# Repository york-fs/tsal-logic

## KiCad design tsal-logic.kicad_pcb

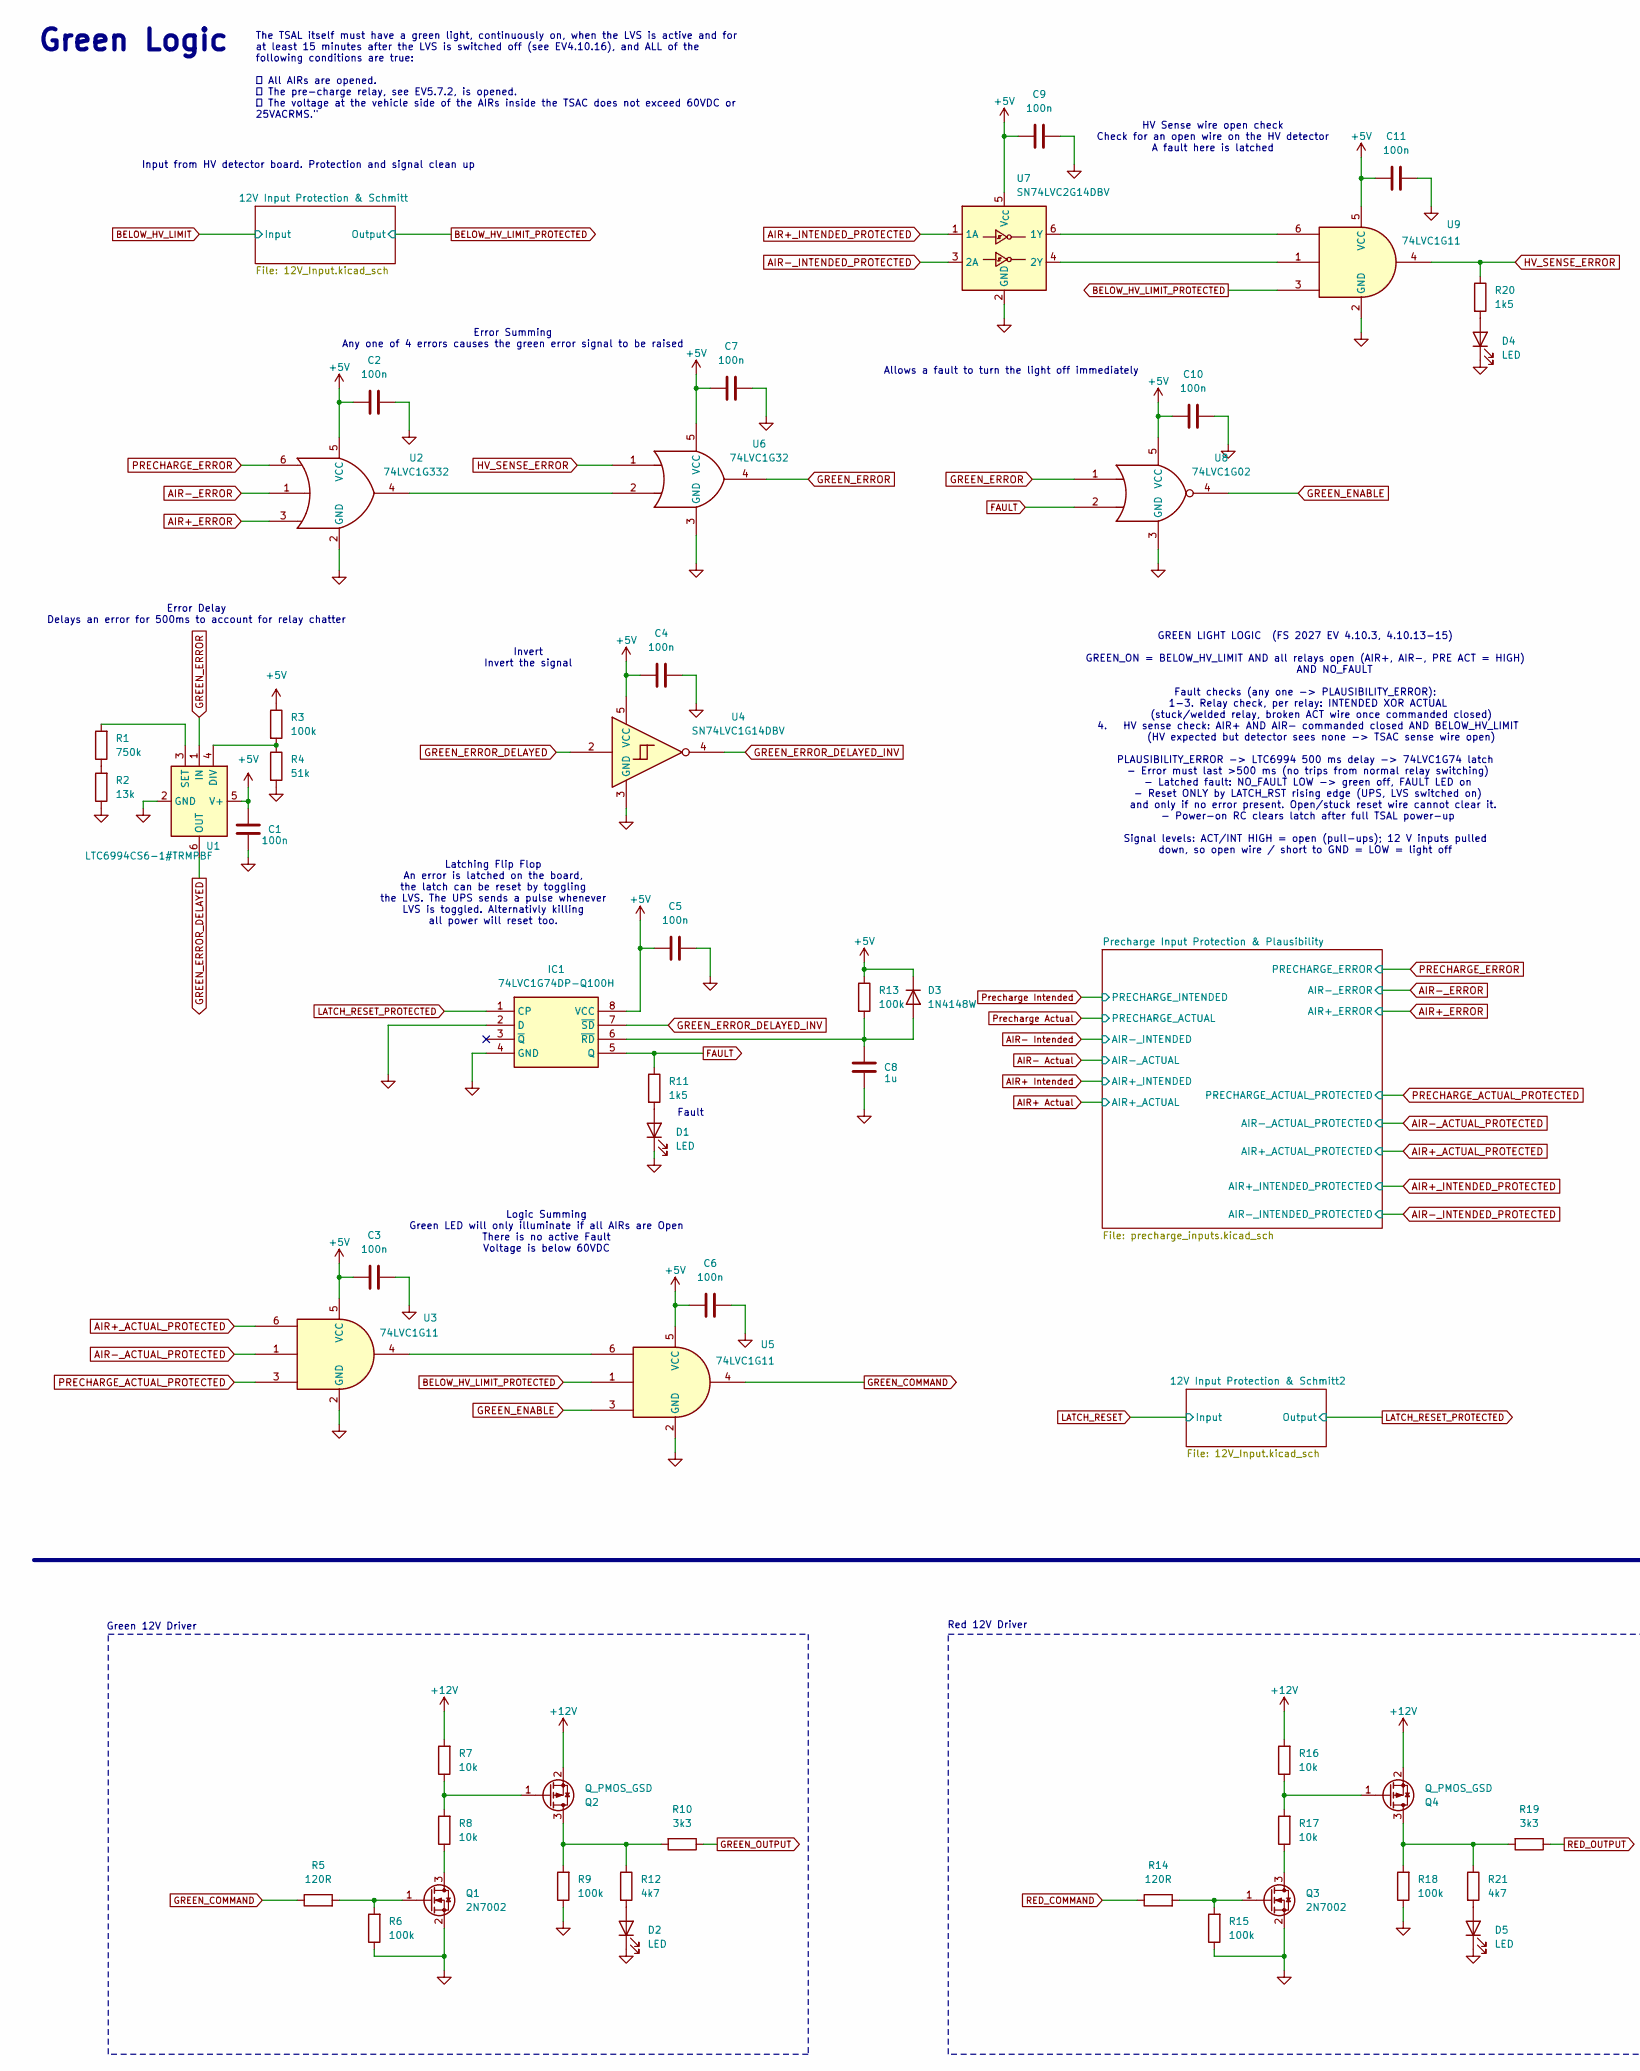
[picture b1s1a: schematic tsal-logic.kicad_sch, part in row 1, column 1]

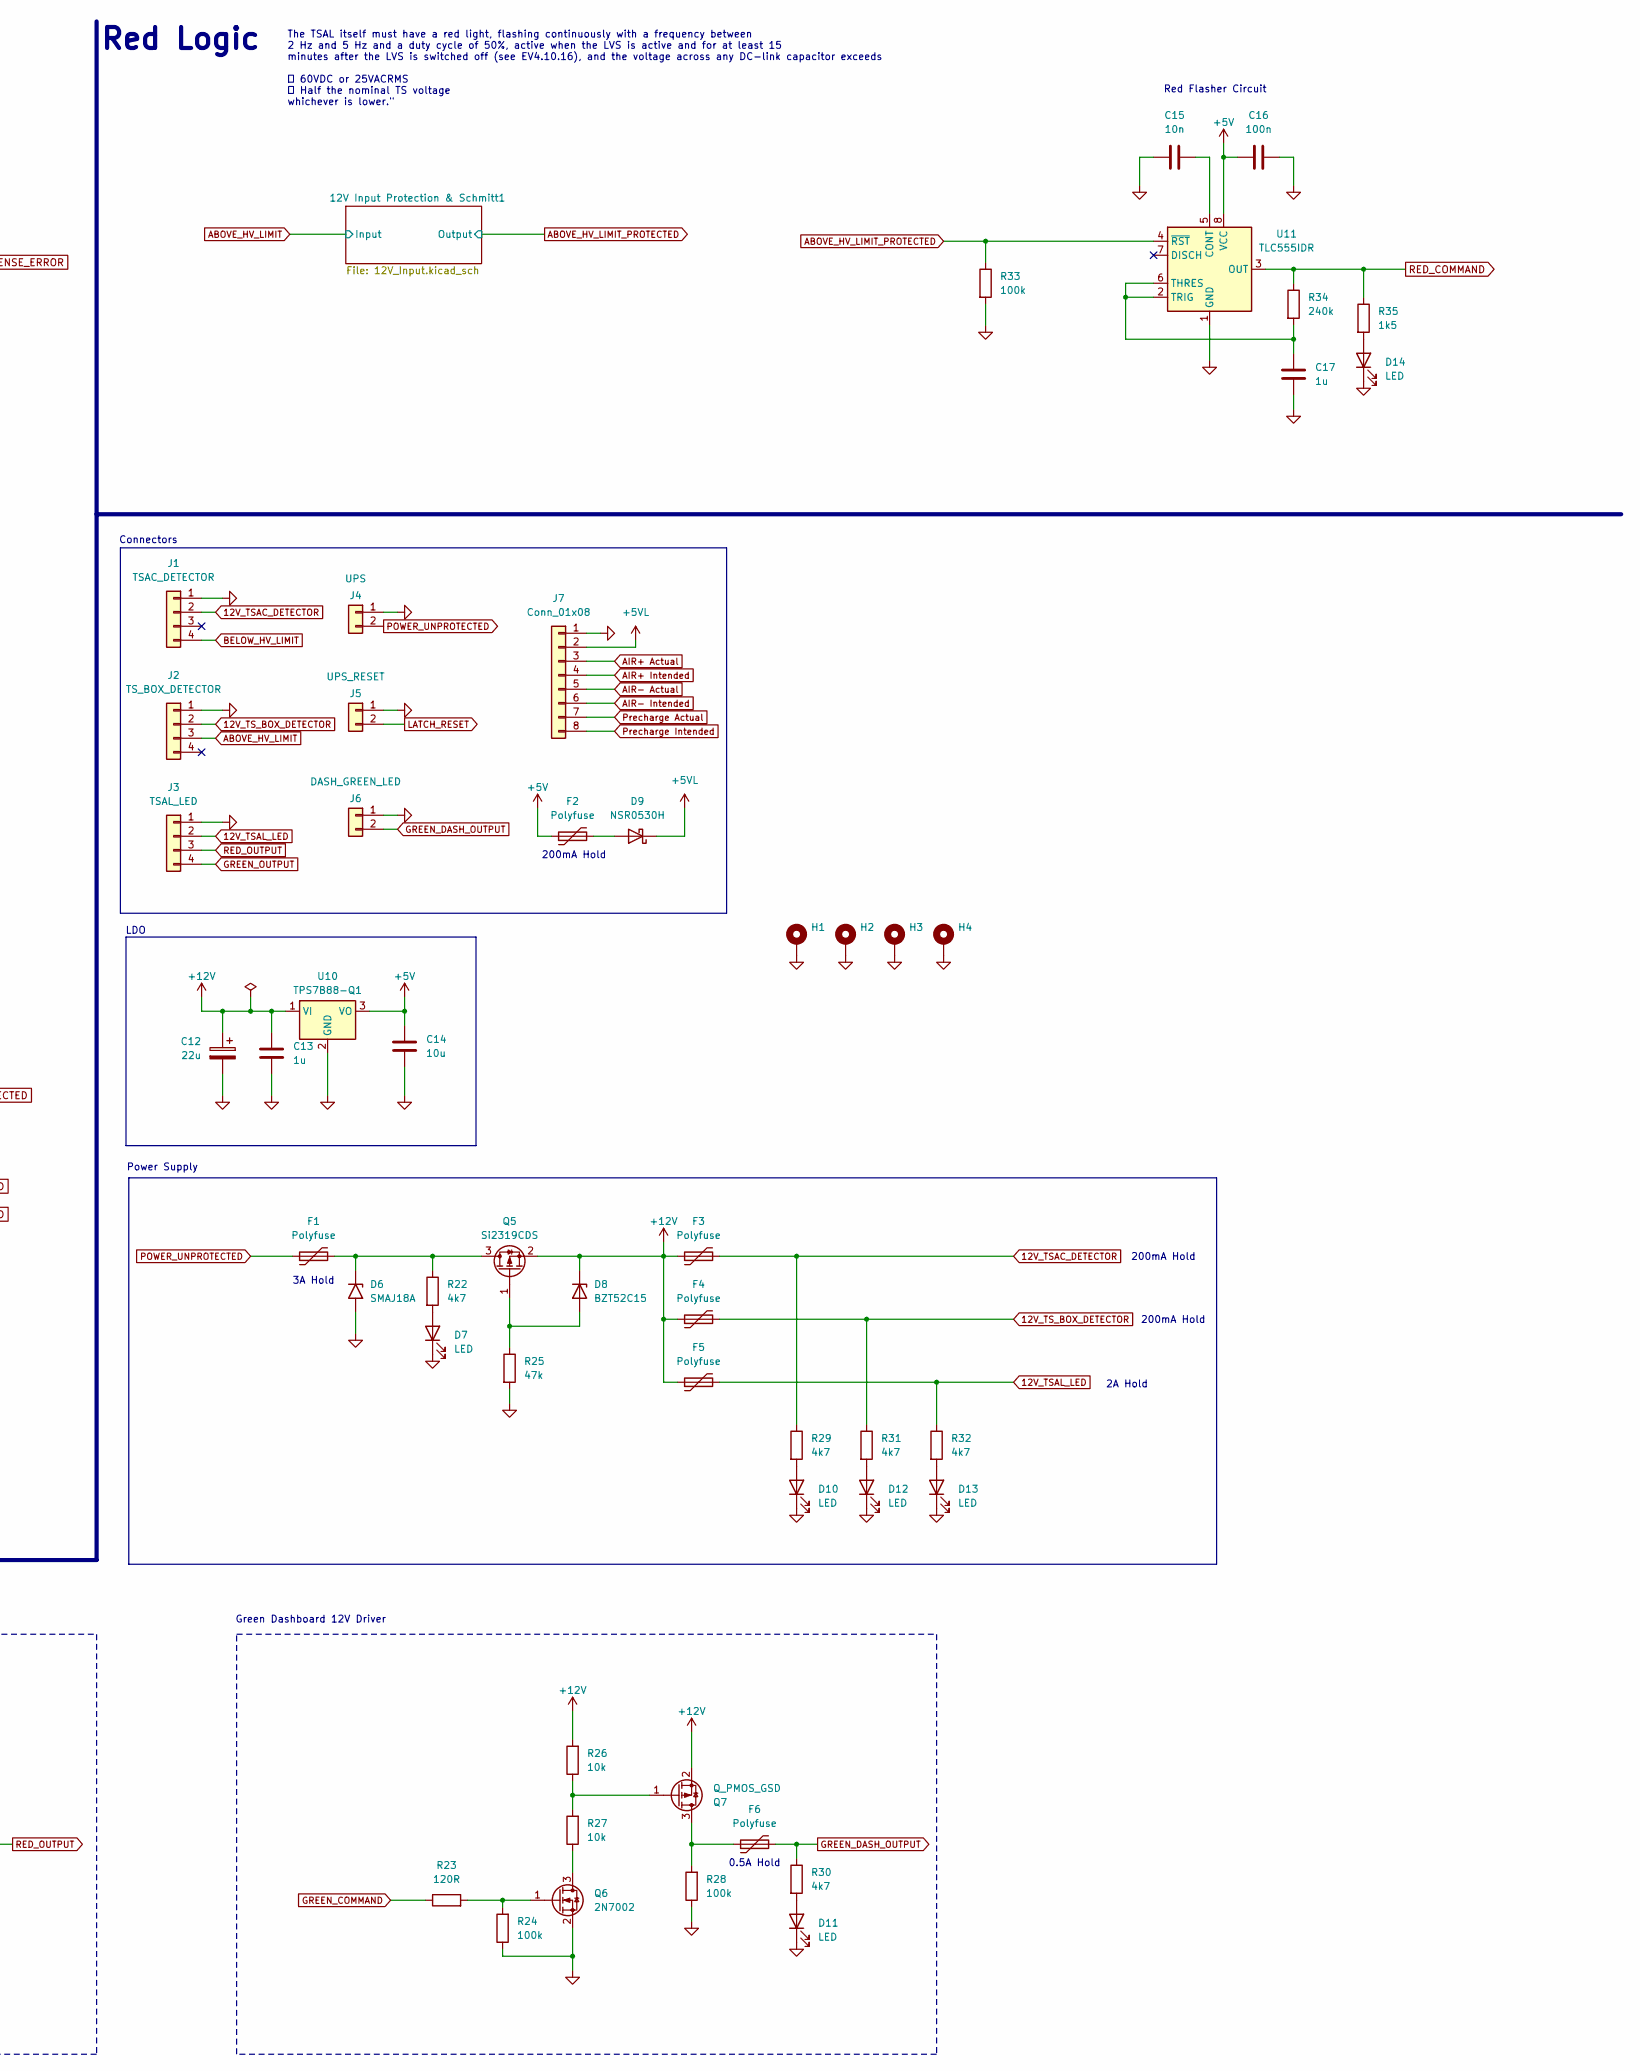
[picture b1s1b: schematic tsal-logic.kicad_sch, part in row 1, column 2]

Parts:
C1, C2, C3, C4, C5, C6, C7, C9, C10, C11, C16: 100n; C_0603_1608Metric
C8, C17: 1u; C_1206_3216Metric
C12: 22u; CP_Elec_6.3x5.8
C13: 1u; C_0603_1608Metric
C14: 10u; C_1206_3216Metric
C15: 10n; C_0603_1608Metric
D1, D2, D4, D5, D7, D10, D11, D12, D13, D14: LED; LED_0603_1608Metric
D3: 1N4148W; D_SOD-123
D6: SMAJ18A; D_SMA
D8: BZT52C15; D_SOD-123; LCSC C19077412
D9: NSR0530H; D_SOD-323F
F1: Polyfuse; Fuse_2920_7451Metric
F2, F3, F4, F6: Polyfuse; Fuse_0805_2012Metric
F5: Polyfuse; Fuse_1210_3225Metric
H1, H2, H3, H4: MountingHole_Pad; MountingHole_3.2mm_M3_Pad_Via
IC1: 74LVC1G74DP-Q100H; TSSOP-8_3x3mm_P0.65mm; Mouser Part Number 771-74LVC1G74DPQ100H
J1: TSAC_DETECTOR; MolexMicrofitPlus1x4
J2: TS_BOX_DETECTOR; MolexMicrofitPlus1x4
J3: TSAL_LED; MolexMicrofitPlus1x4
J4: UPS; MolexMicrofitPlus1x2
J5: UPS_RESET; MolexMicrofitPlus1x2
J6: DASH_GREEN_LED; MolexMicrofitPlus1x2
J7: Conn_01x08; MolexMicrofitPlus2x4
Q1, Q3, Q6: 2N7002; SOT-23
Q2, Q4, Q7: Q_PMOS_GSD; SOT-23; LCSC C150147
Q5: Si2319CDS; SOT-23; LCSC C150147
R1: 750k; R_0603_1608Metric
R2: 13k; R_0603_1608Metric
R3, R6, R9, R13, R15, R18, R24, R28, R33: 100k; R_0603_1608Metric
R4: 51k; R_0603_1608Metric
R5, R14, R23: 120R; R_0603_1608Metric
R7, R8, R16, R17, R26, R27: 10k; R_0603_1608Metric
R10, R19: 3k3; R_0603_1608Metric
R11, R20, R35: 1k5; R_0603_1608Metric
R12, R21, R22, R29, R30, R31, R32: 4k7; R_0603_1608Metric
R25: 47k; R_0603_1608Metric
R34: 240k; R_0603_1608Metric
U1: LTC6994CS6-1#TRMPBF; TSOT-23-6
U2: 74LVC1G332; SOT-23-6
U3, U5, U9: 74LVC1G11; SOT-23-6
U4: SN74LVC1G14DBV; SOT-23-5
U6: 74LVC1G32; SOT-23-5
U7: SN74LVC2G14DBV; SOT-23-6
U8: 74LVC1G02; SOT-23-5
U10: TPS7B88-Q1; TO-252-2
U11: TLC555IDR; SOIC-8_3.9x4.9mm_P1.27mm

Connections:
12V_TSAC_DETECTOR: F3.2, J1.2, R29.1
12V_TSAL_LED: F5.2, J3.2, R32.1
12V_TS_BOX_DETECTOR: F4.2, J2.2, R31.1
+5V: C1.2, C2.1, C3.1, C4.1, C5.1, C6.1, C7.1, C9.1, C10.1, C11.1, C14.1, C16.1, D3.1 (K), F2.1, IC1.8 (VCC), R3.1, R13.1, U1.5 (V+), U2.5 (VCC), U3.5 (VCC), U4.5 (VCC), U5.5 (VCC), U6.5 (VCC), U7.5 (V_{CC}), U8.5 (VCC), U9.5 (VCC), U10.3 (VO), U11.8 (VCC); also elsewhere on the board
+5VL: D9.1 (K), J7.2
+12V: C12.1, C13.1, D8.1 (K), F3.1, F4.1, F5.1, Q2.2 (S), Q4.2 (S), Q5.2 (S), Q7.2 (S), R7.2, R16.2, R26.2, U10.1 (VI)
ABOVE_HV_LIMIT: J2.3; also elsewhere on the board
ABOVE_HV_LIMIT_PROTECTED: R33.1, U11.4 (~RST); also elsewhere on the board
AIR+ Actual: J7.3; also elsewhere on the board
AIR+ Intended: J7.4; also elsewhere on the board
AIR+_ACTUAL_PROTECTED: U3.6; also elsewhere on the board
AIR+_ERROR: U2.3; also elsewhere on the board
AIR+_INTENDED_PROTECTED: U7.1 (1A); also elsewhere on the board
AIR- Actual: J7.5; also elsewhere on the board
AIR- Intended: J7.6; also elsewhere on the board
AIR-_ACTUAL_PROTECTED: U3.1; also elsewhere on the board
AIR-_ERROR: U2.1; also elsewhere on the board
AIR-_INTENDED_PROTECTED: U7.3 (2A); also elsewhere on the board
BELOW_HV_LIMIT: J1.4; also elsewhere on the board
BELOW_HV_LIMIT_PROTECTED: U5.1, U9.3; also elsewhere on the board
FAULT: IC1.5 (Q), R11.1, U8.2
GND: C1.1, C2.2, C3.2, C4.2, C5.2, C6.2, C7.2, C8.1, C9.2, C10.2, C11.2, C12.2, C13.2, C14.2, C15.1, C16.2, C17.1, D1.1 (K), D2.1 (K), D4.1 (K), D5.1 (K), D6.2 (A2), D7.1 (K), D10.1 (K), D11.1 (K), D12.1 (K), D13.1 (K), D14.1 (K), H1.1 (1_1), H2.1 (1_1), H3.1 (1_1), H4.1 (1_1), IC1.2 (D), IC1.4 (GND), J1.1, J2.1, J3.1, J4.1, J5.1, J6.1, J7.1, Q1.2 (S), Q3.2 (S), Q6.2 (S), R2.1, R4.2, R6.1, R9.1, R15.1, R18.1, R24.1, R25.2, R28.1, R33.2, U1.2 (GND), U2.2 (GND), U3.2 (GND), U4.3 (GND), U5.2 (GND), U6.3 (GND), U7.2 (GND), U8.3 (GND), U9.2 (GND), U10.2 (GND), U11.1 (GND); also elsewhere on the board
GREEN_COMMAND: R5.1, R23.1, U5.4
GREEN_DASH_OUTPUT: F6.2, J6.2, R30.1
GREEN_ENABLE: U5.3, U8.4
GREEN_ERROR: U1.1 (IN), U6.4, U8.1
GREEN_ERROR_DELAYED: U1.6 (OUT), U4.2
GREEN_ERROR_DELAYED_INV: IC1.7 (~SD), U4.4
GREEN_OUTPUT: J3.4, R10.1
HV_SENSE_ERROR: R20.1, U6.1, U9.4
LATCH_RESET: J5.2; also elsewhere on the board
LATCH_RESET_PROTECTED: IC1.1 (CP); also elsewhere on the board
unnamed: D1.2 (A), R11.2
unnamed: D2.2 (A), R12.2
unnamed: C8.2, D3.2 (A), IC1.6 (~RD), R13.2
unnamed: D4.2 (A), R20.2
unnamed: D5.2 (A), R21.2
unnamed: D6.1 (A1), F1.2, Q5.3 (D), R22.1
unnamed: D7.2 (A), R22.2
unnamed: D8.2 (A), Q5.1 (G), R25.1
unnamed: D9.2 (A), F2.2
unnamed: D10.2 (A), R29.2
unnamed: D11.2 (A), R30.2
unnamed: D12.2 (A), R31.2
unnamed: D13.2 (A), R32.2
unnamed: D14.2 (A), R35.2
unnamed: Q1.3 (D), R8.1
unnamed: Q1.1 (G), R5.2, R6.2
unnamed: Q2.3 (D), R9.2, R10.2, R12.1
unnamed: Q2.1 (G), R7.1, R8.2
unnamed: Q3.3 (D), R17.1
unnamed: Q3.1 (G), R14.2, R15.2
unnamed: Q4.3 (D), R18.2, R19.2, R21.1
unnamed: Q4.1 (G), R16.1, R17.2
unnamed: Q6.3 (D), R27.1
unnamed: Q6.1 (G), R23.2, R24.2
unnamed: F6.1, Q7.3 (D), R28.2
unnamed: Q7.1 (G), R26.1, R27.2
unnamed: R1.1, R2.2
unnamed: R3.2, R4.1, U1.4 (DIV)
unnamed: R1.2, U1.3 (SET)
unnamed: U2.4, U6.2
unnamed: U3.4, U5.6
unnamed: U7.6 (1Y), U9.6
unnamed: U7.4 (2Y), U9.1
unnamed: C15.2, U11.5 (CONT)
unnamed: C17.2, R34.2, U11.2 (TRIG), U11.6 (THRES)
POWER_UNPROTECTED: F1.1, J4.2
PRECHARGE_ACTUAL_PROTECTED: U3.3; also elsewhere on the board
PRECHARGE_ERROR: U2.6; also elsewhere on the board
Precharge Actual: J7.7; also elsewhere on the board
Precharge Intended: J7.8; also elsewhere on the board
RED_COMMAND: R14.1, R34.1, R35.1, U11.3 (OUT)
RED_OUTPUT: J3.3, R19.1

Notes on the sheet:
Latching Flip Flop An error is latched on the board, the latch can be reset by toggling the LVS. The UPS sends a pulse whenever LVS is toggled. Alternativly killing all power will reset too.
0.5A Hold
GREEN LIGHT LOGIC (FS 2027 EV 4.10.3, 4.10.13-15) GREEN_ON = BELOW_HV_LIMIT AND all relays open (AIR+, AIR-, PRE ACT = HIGH) AND NO_FAULT Fault checks (any one -> PLAUSIBILITY_ERROR): 1-3. Relay check, per relay: INTENDED XOR ACTUAL (stuck/welded relay, broken ACT wire once commanded closed) 4. HV 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
200mA Hold
LDO
Error Summing Any one of 4 errors causes the green error signal to be raised
Input from HV detector board. Protection and signal clean up
Power Supply
2A Hold
The TSAL itself must have a green light, continuously on, when the LVS is active and for at least 15 minutes after the LVS is switched off (see EV4.10.16), and ALL of the following conditions are true:  All AIRs are opened.  The pre-charge relay, see EV5.7.2, is opened.  The voltage at the vehic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
HV Sense wire open check Check for an open wire on the HV detector A fault here is latched
Red 12V Driver
Error Delay Delays an error for 500ms to account for relay chatter
Green 12V Driver
Red Flasher Circuit
Invert Invert the signal
Allows a fault to turn the light off immediately
3A Hold
Logic Summing Green LED will only illuminate if all AIRs are Open There is no active Fault Voltage is below 60VDC
Fault
Green Dashboard 12V Driver
The TSAL itself must have a red light, flashing continuously with a frequency between 2 Hz and 5 Hz and a duty cycle of 50%, active when the LVS is active and for at least 15 minutes after the LVS is switched off (see EV4.10.16), and the voltage across any DC-link capacitor exceeds  60VDC or 25VAC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
Connectors
Red Logic
Green Logic

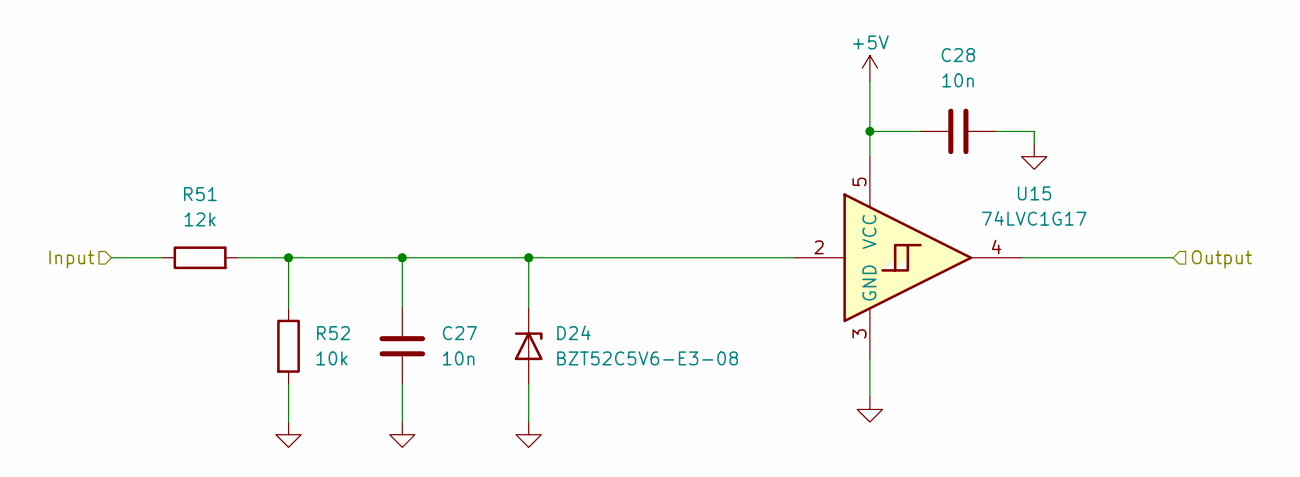
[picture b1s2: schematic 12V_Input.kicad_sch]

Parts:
C27, C28: 10n; C_0603_1608Metric
D24: BZT52C5V6-E3-08; D_SOD-123; LCSC C19077412
R51: 12k; R_0603_1608Metric
R52: 10k; R_0603_1608Metric
U15: 74LVC1G17; SOT-23-5

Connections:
+5V: C28.1, U15.5 (VCC); also elsewhere on the board
BELOW_HV_LIMIT: R51.1; also elsewhere on the board
BELOW_HV_LIMIT_PROTECTED: U15.4; also elsewhere on the board
GND: C27.2, C28.2, D24.2 (A), R52.2, U15.3 (GND); also elsewhere on the board
unnamed: C27.1, D24.1 (K), R51.2, R52.1, U15.2

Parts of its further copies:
C29, C30, C31, C32: 10n; C_0603_1608Metric
D25, D26: BZT52C5V6-E3-08; D_SOD-123; LCSC C19077412
R53, R55: 12k; R_0603_1608Metric
R54, R56: 10k; R_0603_1608Metric
U16, U17: 74LVC1G17; SOT-23-5

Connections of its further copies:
+5V: C30.1, C32.1, U16.5 (VCC), U17.5 (VCC); also elsewhere on the board
ABOVE_HV_LIMIT: R53.1; also elsewhere on the board
ABOVE_HV_LIMIT_PROTECTED: U16.4; also elsewhere on the board
GND: C29.2, C30.2, C31.2, C32.2, D25.2 (A), D26.2 (A), R54.2, R56.2, U16.3 (GND), U17.3 (GND); also elsewhere on the board
LATCH_RESET: R55.1; also elsewhere on the board
LATCH_RESET_PROTECTED: U17.4; also elsewhere on the board
unnamed: C29.1, D25.1 (K), R53.2, R54.1, U16.2
unnamed: C31.1, D26.1 (K), R55.2, R56.1, U17.2

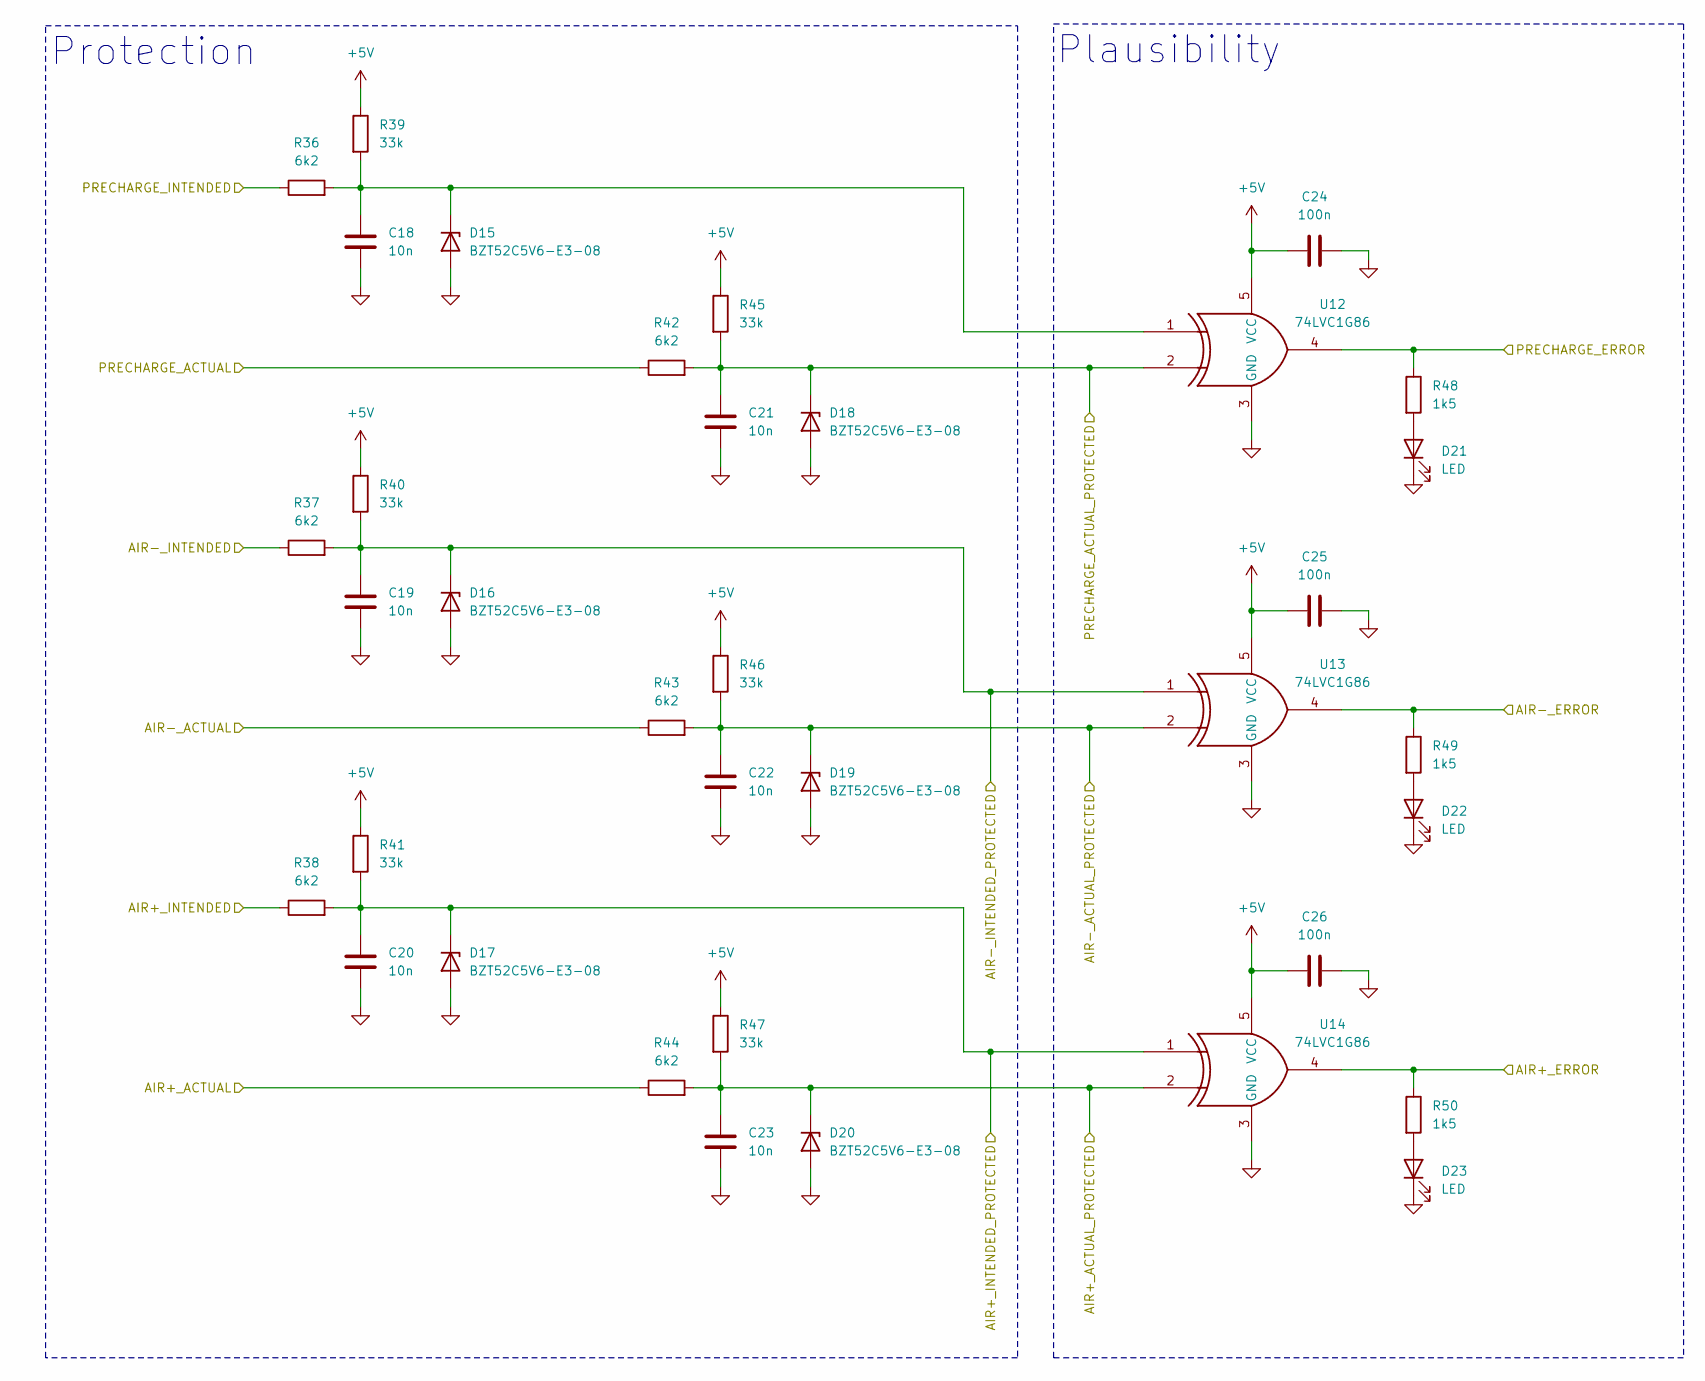
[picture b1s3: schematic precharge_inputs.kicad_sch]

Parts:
C18, C19, C20, C21, C22, C23: 10n; C_0603_1608Metric
C24, C25, C26: 100n; C_0603_1608Metric
D15, D16, D17, D18, D19, D20: BZT52C5V6-E3-08; D_SOD-123; LCSC C19077412
D21, D22, D23: LED; LED_0603_1608Metric
R36, R37, R38, R42, R43, R44: 6k2; R_0603_1608Metric
R39, R40, R41, R45, R46, R47: 33k; R_0603_1608Metric
R48, R49, R50: 1k5; R_0603_1608Metric
U12, U13, U14: 74LVC1G86; SOT-23-5

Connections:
+5V: C24.1, C25.1, C26.1, R39.1, R40.1, R41.1, R45.1, R46.1, R47.1, U12.5 (VCC), U13.5 (VCC), U14.5 (VCC); also elsewhere on the board
AIR+ Actual: R44.1; also elsewhere on the board
AIR+ Intended: R38.1; also elsewhere on the board
AIR+_ACTUAL_PROTECTED: C23.1, D20.1 (K), R44.2, R47.2, U14.2; also elsewhere on the board
AIR+_ERROR: R50.1, U14.4; also elsewhere on the board
AIR+_INTENDED_PROTECTED: C20.1, D17.1 (K), R38.2, R41.2, U14.1; also elsewhere on the board
AIR- Actual: R43.1; also elsewhere on the board
AIR- Intended: R37.1; also elsewhere on the board
AIR-_ACTUAL_PROTECTED: C22.1, D19.1 (K), R43.2, R46.2, U13.2; also elsewhere on the board
AIR-_ERROR: R49.1, U13.4; also elsewhere on the board
AIR-_INTENDED_PROTECTED: C19.1, D16.1 (K), R37.2, R40.2, U13.1; also elsewhere on the board
GND: C18.2, C19.2, C20.2, C21.2, C22.2, C23.2, C24.2, C25.2, C26.2, D15.2 (A), D16.2 (A), D17.2 (A), D18.2 (A), D19.2 (A), D20.2 (A), D21.1 (K), D22.1 (K), D23.1 (K), U12.3 (GND), U13.3 (GND), U14.3 (GND); also elsewhere on the board
unnamed: C18.1, D15.1 (K), R36.2, R39.2, U12.1
unnamed: D21.2 (A), R48.2
unnamed: D22.2 (A), R49.2
unnamed: D23.2 (A), R50.2
PRECHARGE_ACTUAL_PROTECTED: C21.1, D18.1 (K), R42.2, R45.2, U12.2; also elsewhere on the board
PRECHARGE_ERROR: R48.1, U12.4; also elsewhere on the board
Precharge Actual: R42.1; also elsewhere on the board
Precharge Intended: R36.1; also elsewhere on the board

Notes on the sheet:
Plausibility
Protection

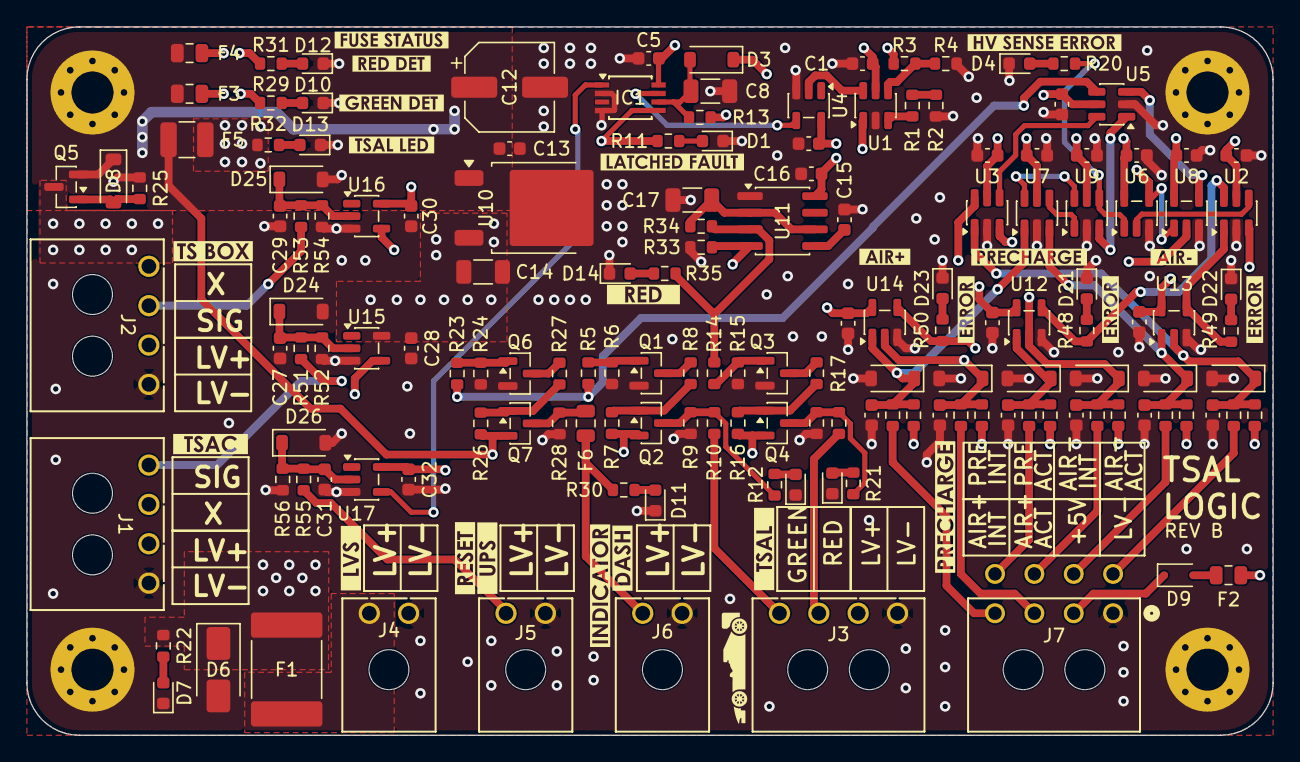
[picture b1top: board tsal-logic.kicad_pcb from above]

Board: 4 copper layers, 95.0 x 54.0 mm, 178 parts (0 on the bottom side), 81 nets.

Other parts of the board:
kibuzzard-6AF2F854: G***; kibuzzard-6AF2F854
kibuzzard-6AF25BAC: G***; kibuzzard-6AF25BAC
kibuzzard-6AF258D0, kibuzzard-6AF258D0#2, kibuzzard-6AF258D0#3: G***; kibuzzard-6AF258D0
kibuzzard-6AF258EB: G***; kibuzzard-6AF258EB
kibuzzard-6AF258FB: G***; kibuzzard-6AF258FB
kibuzzard-6AF345D6: G***; kibuzzard-6AF345D6
kibuzzard-6AF345EE: G***; kibuzzard-6AF345EE
kibuzzard-6AF3020A: G***; kibuzzard-6AF3020A
kibuzzard-6AF3445E: G***; kibuzzard-6AF3445E
kibuzzard-6AF3447E: G***; kibuzzard-6AF3447E
kibuzzard-6AF3449C: G***; kibuzzard-6AF3449C
kibuzzard-6AF3917F: G***; kibuzzard-6AF3917F
kibuzzard-6AF25902: G***; kibuzzard-6AF25902
kibuzzard-6AF25947: G***; kibuzzard-6AF25947
kibuzzard-6AF30218: G***; kibuzzard-6AF30218
kibuzzard-6AF30225: G***; kibuzzard-6AF30225
kibuzzard-6AF34707: G***; kibuzzard-6AF34707
kibuzzard-6AF35645: G***; kibuzzard-6AF35645
kibuzzard-6AF39142: G***; kibuzzard-6AF39142
kibuzzard-6AFB0BD4: G***; kibuzzard-6AFB0BD4

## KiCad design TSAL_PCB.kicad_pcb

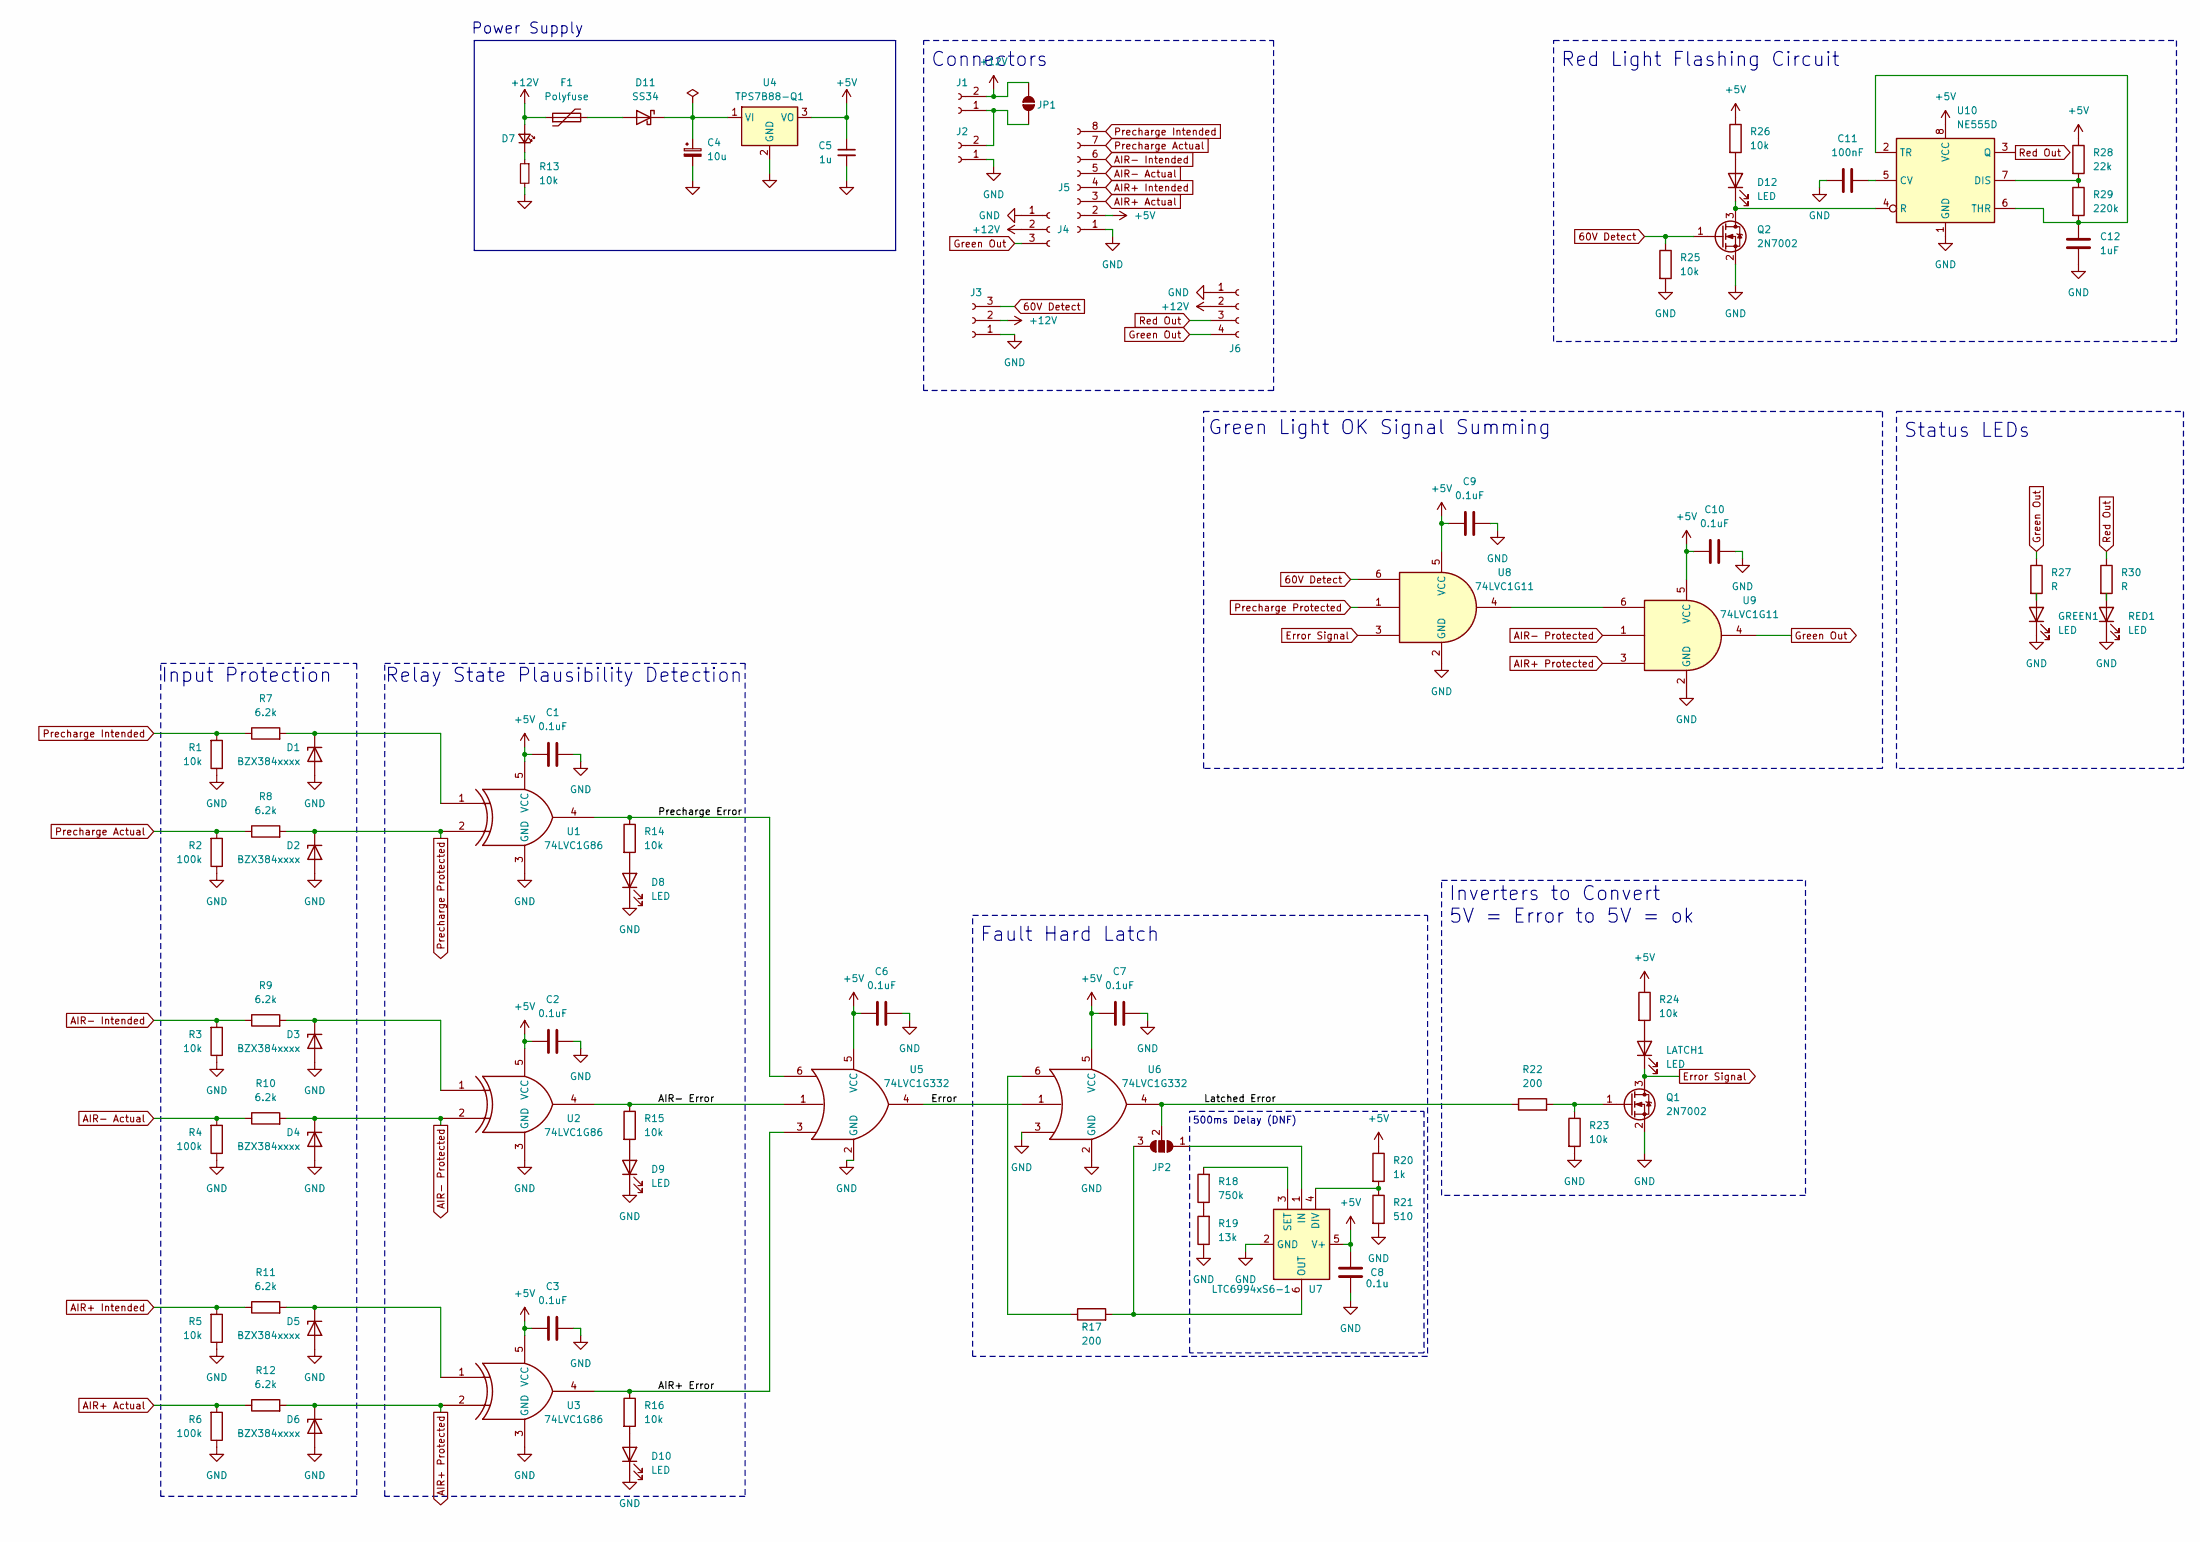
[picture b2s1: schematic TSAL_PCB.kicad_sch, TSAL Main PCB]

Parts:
C1, C2, C3, C6, C7, C9, C10: 0.1uF; C_0603_1608Metric
C4: 10u; CP_Elec_6.3x5.4
C5: 1u; C_0603_1608Metric
C8: 0.1u; C_0603_1608Metric
C11: 100nF; C_0603_1608Metric
C12: 1uF; C_0603_1608Metric
D1, D2, D3, D4, D5, D6: BZX384xxxx; D_SOD-323
D7: LED_Small; LED_0603_1608Metric
D8, D9, D10, D12: LED; LED_0603_1608Metric
D11: SS34; D_SMA
F1: Polyfuse; R_0805_2012Metric
GREEN1: LED; LED_0603_1608Metric
J1, J2: Conn_01x02_Socket; MolexMicrofitPlus1x2
J3, J4: Conn_01x03_Socket; MolexMicrofitPlus1x3
J5: Conn_01x08_Socket; MolexMicrofitPlus1x8
J6: Conn_01x04_Socket; MolexMicrofitPlus1x4
JP1: SolderJumper_2_Open; SolderJumper-2_P1.3mm_Open_RoundedPad1.0x1.5mm
JP2: SolderJumper_3_Open; SolderJumper-3_P1.3mm_Open_RoundedPad1.0x1.5mm_NumberLabels
LATCH1: LED; LED_0603_1608Metric
Q1, Q2: 2N7002; SOT-23
R1, R3, R5, R13, R14, R15, R16, R23, R24, R25, R26: 10k; R_0603_1608Metric
R2, R4, R6: 100k; R_0603_1608Metric
R7, R8, R9, R10, R11, R12: 6.2k; R_0603_1608Metric
R17, R22: 200; R_0603_1608Metric
R18: 750k; R_0603_1608Metric
R19: 13k; R_0603_1608Metric
R20: 1k; R_0603_1608Metric
R21: 510; R_0603_1608Metric
R27, R30: R; R_0603_1608Metric
R28: 22k; R_0603_1608Metric
R29: 220k; R_0603_1608Metric
RED1: LED; LED_0603_1608Metric
U1, U2, U3: 74LVC1G86; SOT-23-5
U4: TPS7B88-Q1; TO-252-2
U5, U6: 74LVC1G332; SOT-23-6
U7: LTC6994xS6-1; TSOT-23-6
U8, U9: 74LVC1G11; SOT-23-6
U10: NE555D; SOIC-8_3.9x4.9mm_P1.27mm

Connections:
60V Detect: J3.3, Q2.1 (G), R25.1, U8.6
+5V: C1.1, C2.1, C3.1, C5.1, C6.1, C7.1, C8.2, C9.1, C10.1, J5.2, R20.1, R24.1, R26.1, R28.1, U1.5 (VCC), U2.5 (VCC), U3.5 (VCC), U4.3 (VO), U5.5 (VCC), U6.5 (VCC), U7.5 (V+), U8.5 (VCC), U9.5 (VCC), U10.8 (VCC)
+12V: D7.2 (A), F1.1, J1.2, J3.2, J4.2, J6.2, JP1.2 (B)
/AIR+ Error: R16.1, U3.4, U5.3
/AIR- Error: R15.1, U2.4, U5.1
/Error: U5.4, U6.1
/Latched Error: JP2.2 (C), R22.1, U6.4
/Precharge Error: R14.1, U1.4, U5.6
AIR+ Actual: J5.3, R6.2, R12.1
AIR+ Intended: J5.4, R5.2, R11.1
AIR+ Protected: D6.1 (K), R12.2, U3.2, U9.3
AIR- Actual: J5.5, R4.2, R10.1
AIR- Intended: J5.6, R3.2, R9.1
AIR- Protected: D4.1 (K), R10.2, U2.2, U9.1
Error Signal: LATCH1.1 (K), Q1.3 (D), U8.3
GND: C1.2, C2.2, C3.2, C4.2, C5.2, C6.2, C7.2, C8.1, C9.2, C10.2, C11.2, C12.1, D1.2 (A), D2.2 (A), D3.2 (A), D4.2 (A), D5.2 (A), D6.2 (A), D8.1 (K), D9.1 (K), D10.1 (K), GREEN1.1 (K), J2.1, J3.1, J4.1, J5.1, J6.1, Q1.2 (S), Q2.2 (S), R1.1, R2.1, R3.1, R4.1, R5.1, R6.1, R13.2, R19.1, R21.2, R23.2, R25.2, RED1.1 (K), U1.3 (GND), U2.3 (GND), U3.3 (GND), U4.2 (GND), U5.2 (GND), U6.2 (GND), U6.3, U7.2 (GND), U8.2 (GND), U9.2 (GND), U10.1 (GND)
Green Out: J4.3, J6.4, R27.1, U9.4
unnamed: D1.1 (K), R7.2, U1.1
unnamed: D3.1 (K), R9.2, U2.1
unnamed: D5.1 (K), R11.2, U3.1
unnamed: D7.1 (K), R13.1
unnamed: D8.2 (A), R14.2
unnamed: D9.2 (A), R15.2
unnamed: D10.2 (A), R16.2
unnamed: D11.2 (A), F1.2
unnamed: C4.1, D11.1 (K), U4.1 (VI)
unnamed: D12.2 (A), R26.2
unnamed: D12.1 (K), Q2.3 (D), U10.4 (R)
unnamed: GREEN1.2 (A), R27.2
unnamed: J1.1, J2.2, JP1.1 (A)
unnamed: JP2.1 (A), U7.1 (IN)
unnamed: JP2.3 (B), R17.2, U7.6 (OUT)
unnamed: LATCH1.2 (A), R24.2
unnamed: Q1.1 (G), R22.2, R23.1
unnamed: R17.1, U6.6
unnamed: R18.1, R19.2
unnamed: R30.2, RED1.2 (A)
unnamed: R20.2, R21.1, U7.4 (DIV)
unnamed: R18.2, U7.3 (SET)
unnamed: U8.4, U9.6
unnamed: C11.1, U10.5 (CV)
unnamed: R28.2, R29.1, U10.7 (DIS)
unnamed: C12.2, R29.2, U10.2 (TR), U10.6 (THR)
Precharge Actual: J5.7, R2.2, R8.1
Precharge Intended: J5.8, R1.2, R7.1
Precharge Protected: D2.1 (K), R8.2, U1.2, U8.1
Red Out: J6.3, R30.1, U10.3 (Q)

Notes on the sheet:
Green Light OK Signal Summing
Relay State Plausibility Detection
Connectors
500ms Delay (DNF)
Power Supply
Inverters to Convert 5V = Error to 5V = ok
Input Protection
Fault Hard Latch
Red Light Flashing Circuit
Status LEDs
